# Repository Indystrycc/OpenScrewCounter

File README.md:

Designed by [Nikodem Bartnik](https://www.youtube.com/nikodembartnik). 

OpenScrewCounter is a machine built to count various small screws. It was built to simplify the counting procedure of set of screws for [IndyMill CNC machine](http://indystry.cc/indymill/). Researching similar solutions resulted in rejecting a few early ideas for the design of this project and in the end a approach presented above was implemented. At this stage the machine is not perfect and some upgrades are required to make it production ready. 

## Open Source
Project is open source and all the files and the code are available above. Feel free to use it, modify and share with others. Contributing to the project is more than welcome! 

## Parts
 - [Raspberry Pi Pico](https://amzn.to/3FnSxVT)
 - [Motor](https://amzn.to/405kJVr)
 - [7 segment display](https://bit.ly/40bwYQB)
 - [Buttons](https://amzn.to/3yK9nul)
 - [6804 Bearing](https://amzn.to/40ppZDR)
 - [Some screws](https://amzn.to/3leCWBm)

## Videos

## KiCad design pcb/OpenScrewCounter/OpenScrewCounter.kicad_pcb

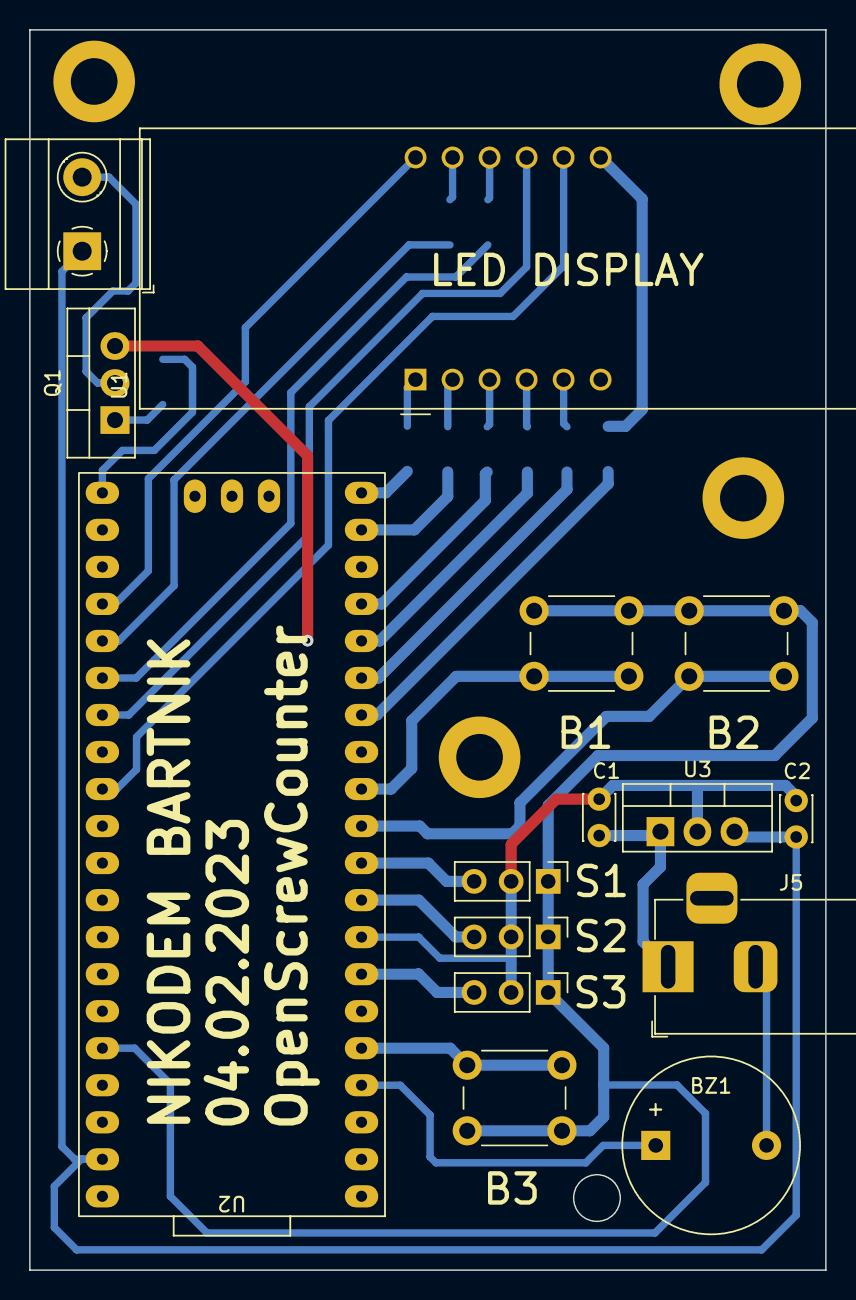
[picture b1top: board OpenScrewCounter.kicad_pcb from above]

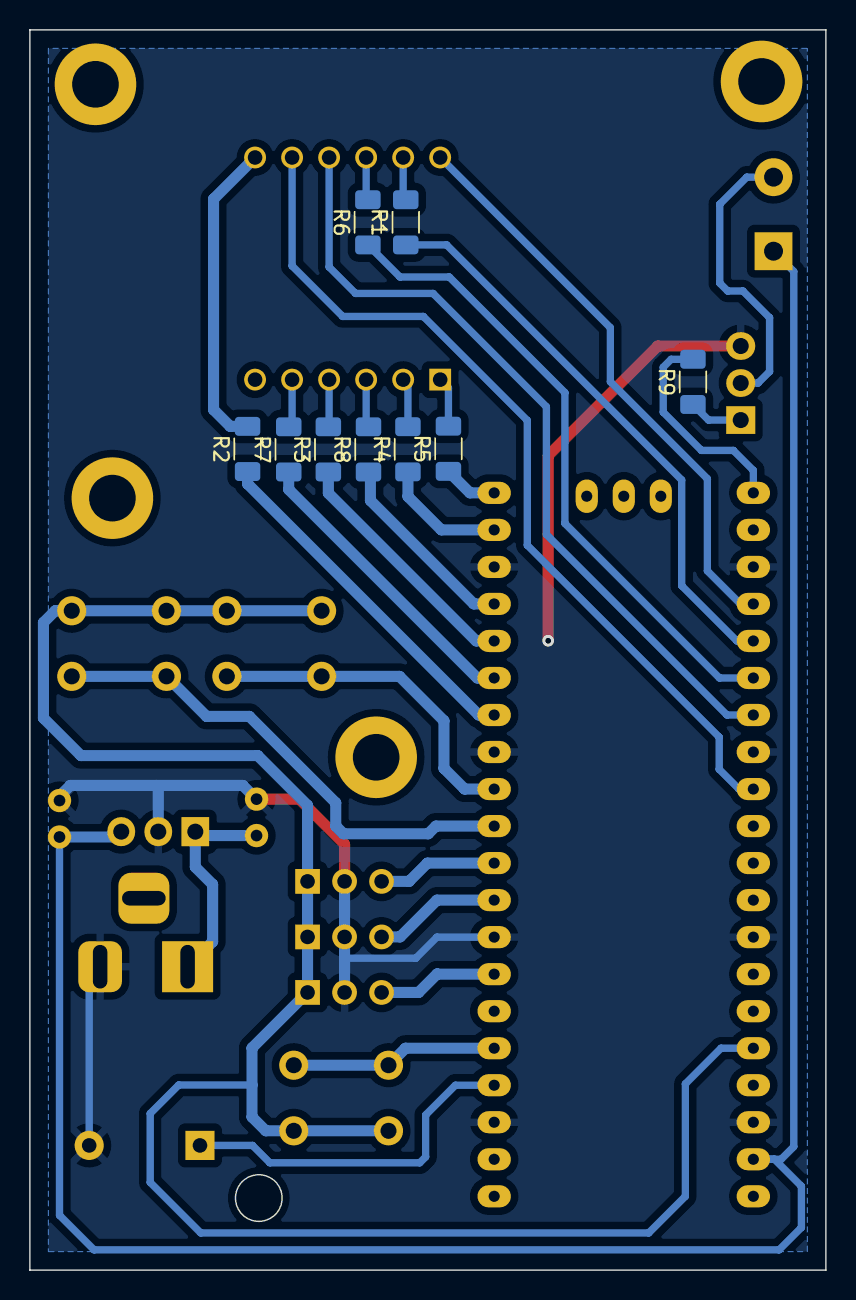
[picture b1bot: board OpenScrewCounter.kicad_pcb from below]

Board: 2 copper layers, 54.6 x 85.1 mm, 24 parts (9 on the bottom side), 33 nets.

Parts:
BZ1: Buzzer; Buzzer_12x9.5RM7.6
C1: 100u; C_Disc_D3.0mm_W2.0mm_P2.50mm
C2: 10u; C_Disc_D3.0mm_W2.0mm_P2.50mm
J2: P1; TerminalBlock_Phoenix_MKDS-1,5-2-5.08_1x02_P5.08mm_Horizont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
J5: Barrel_Jack_MountingPin; BarrelJack_Horizontal
Q1: IRFZ44N; TO-220-3_Vertical
R1, R2, R3, R4, R5, R6, R7, R8: 330; R_1206_3216Metric_Pad1.30x1.75mm_HandSolder
R9: 10k; R_1206_3216Metric_Pad1.30x1.75mm_HandSolder
S1, S2, S3: Sensor; PinHeader_1x03_P2.54mm_Vertical
SW1, SW2, SW3: SW_Push; SW_PUSH_6mm_H7.3mm
U1: CA56-12EWA
U2: pi pico; raspberry pi pico
U3: L7805; TO-220-3_Vertical

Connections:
+3V3: S1.1, S2.1, S3.1, SW1.1, SW2.1, SW3.1, U2.36 (3V3(OUT))
+5V: C2.1, J2.1, U2.39 (VSYS), U3.3 (OUT)
+12V: C1.1, J5.1, U3.1 (IN)
BUTTON1: SW3.2, U2.5 (GP3)
BUTTON2: SW2.2, U2.11 (GP8)
BUTTON3: SW1.2, U2.12 (GP9)
BUZZER: BZ1.1 (-), U2.4 (GP2)
DIG1: U1.12 (CA1), U2.24 (GP18)
DIG2: U1.9 (CA2), U2.27 (GP21)
DIG3: U1.8 (CA3), U2.29 (GP22)
DIS_A: R1.1, U2.25 (GP19)
DIS_B: R2.1, U2.14 (GP10)
DIS_C: R3.1, U2.16 (GP12)
DIS_D: R4.1, U2.19 (GP14)
DIS_DP: R8.1, U2.17 (GP13)
DIS_E: R5.1, U2.20 (GP15)
DIS_F: R6.1, U2.26 (GP20)
DIS_G: R7.1, U2.15 (GP11)
GND: BZ1.2 (+), C1.2, C2.2, J5.2, Q1.3 (S), S1.2, S2.2, S3.2, U2.3 (GND), U2.8 (GND), U2.13 (GND), U2.18 (GND), U2.23 (GND), U2.28 (GND), U2.33 (GND), U2.38 (GND), U3.2 (GND)
MOTOR: R9.2, U2.21 (GP16)
unnamed: J2.2, Q1.2 (D)
unnamed: Q1.1 (G), R9.1
unnamed: R1.2, U1.11 (a)
unnamed: R2.2, U1.7 (b)
unnamed: R3.2, U1.4 (c)
unnamed: R4.2, U1.2 (d)
unnamed: R5.2, U1.1 (e)
unnamed: R6.2, U1.10 (f)
unnamed: R7.2, U1.5 (g)
unnamed: R8.2, U1.3 (DPX)
SENSOR1: S1.3, U2.10 (GP7)
SENSOR2: S2.3, U2.9 (GP6)
SENSOR3: S3.3, U2.7 (GP5)

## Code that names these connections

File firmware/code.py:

from machine import Pin, ADC, Timer, PWM
from time import sleep
import time

motor = PWM(Pin(16))
motor.freq(1000)

buzzer = Pin(2, Pin.OUT)

DIS_A = Pin(19, Pin.OUT)
DIS_B = Pin(10, Pin.OUT)
DIS_C = Pin(12, Pin.OUT)
DIS_D = Pin(14, Pin.OUT)
DIS_E = Pin(15, Pin.OUT)
DIS_F = Pin(20, Pin.OUT)
DIS_G = Pin(11, Pin.OUT)
DIS_DP = Pin(13, Pin.OUT)

DIS_DIG_1 = Pin(18, Pin.OUT)
DIS_DIG_2 = Pin(21, Pin.OUT)
DIS_DIG_3 = Pin(22, Pin.OUT)

dis_value = 0

all_segments = [DIS_A, DIS_B, DIS_C, DIS_D, DIS_E, DIS_F, DIS_G, DIS_DP]
segments = {
    0: [DIS_A, DIS_B, DIS_C, DIS_D, DIS_E, DIS_F],
    1: [DIS_B, DIS_C],
    2: [DIS_A, DIS_B, DIS_G, DIS_E, DIS_D],
    3: [DIS_A, DIS_B, DIS_C, DIS_D, DIS_G],
    4: [DIS_F, DIS_G, DIS_B, DIS_C],
    5: [DIS_A, DIS_F, DIS_G, DIS_C, DIS_D],
    6: [DIS_A, DIS_F, DIS_E, DIS_D, DIS_C, DIS_G],
    7: [DIS_A, DIS_B, DIS_C],
    8: [DIS_A, DIS_B, DIS_C, DIS_D, DIS_E, DIS_F, DIS_G],
    9: [DIS_A, DIS_B, DIS_C, DIS_D, DIS_F, DIS_G]
}

def pad_with_zeros(number, length=3):
    number_str = str(number)
    while len(number_str) < length:
        number_str = '0' + number_str
    return number_str

def display_number(number):
    # Convert the number to a string and pad it with leading zeros if necessary
    number_str = pad_with_zeros(number)
    # Loop through each digit
    for i in range(3):
        # Activate the appropriate digit pin
        if i == 0:
            DIS_DIG_1.value(1)
            DIS_DIG_2.value(0)
            DIS_DIG_3.value(0)
        elif i == 1:
            DIS_DIG_1.value(0)
            DIS_DIG_2.value(1)
            DIS_DIG_3.value(0)
        else:
            DIS_DIG_1.value(0)
            DIS_DIG_2.value(0)
            DIS_DIG_3.value(1)
        # Get the segments for the current digit
        segments_for_digit = segments[int(number_str[i])]
        # Turn on the segments for the current digit
        for segment in segments_for_digit:
            segment.value(0)
        # Wait for a short time to allow the human eye to see the digits
        sleep(0.002)
        # Turn off the segments for the current digit
        for segment in all_segments:
            segment.value(1)
            
def timer_callback(timer):
    display_number(dis_value)


led = Pin(25, Pin.OUT)
sen = machine.ADC(26)
print('ready')
timer= Timer(mode=Timer.PERIODIC, period=5, callback=timer_callback)


def motorOn():
    motor.duty_u16(50000)


def motorOff():
    motor.duty_u16(0)


def countOneScrew():
    motorOn()
    while(sen.read_u16() < 13000):
        pass
    motorOff()
    sleep(0.02)
    return True

        
def countScrews(amount):
    global dis_value
    counter = 0
    for x in range(amount):
        countOneScrew()
        counter += 1
        dis_value = counter
        
def beep():
    for x in range(2):
        buzzer.on()
        sleep(0.1)
        buzzer.off()
        sleep(0.05)

while(1):
    dis_value = 0
    countScrews(10)
    sleep(0.3)
    beep()
    sleep(3)

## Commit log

2023-02-03 added initial PCB files
2023-02-04 testing script LCD and buzzer
2023-02-04 new version of slide2
2023-02-04 drum update
2023-02-04 pcb update
2023-02-14 pcb gcode and fix
2023-02-14 printed files update
2023-02-21 update printed parts
2023-02-21 add plates dxf files
2023-02-21 update printed files
2023-02-21 added files for PCB
2023-03-23 added readme
2023-03-23 added project picture
2023-03-23 PCB clean up
2023-03-23 readme fix
